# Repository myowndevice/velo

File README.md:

## Велокомпьютер

Велокомпьютер (англ. Cyclocomputer; в просторечии — Велосчётчик) — электронное устройство для измерения скорости и пробега велосипеда, а также дополнительных параметров, таких как средняя скорость, время в пути, максимальная скорость, каденс (частота вращения педалей) и другие.

Вы можете самостоятельно сделать этот современный прибор. Прибор базируется на микроконтроллере STM8 и позволит вам приобрести навыки программирования микроконтроллеров. Он имеет отличные, современные характеристики:

- Управление и передача информации по bluetooth (экран отсутствует), например на смартфон
- Учёт основных показателей — текущая скорость, максимальная скорость, активное время поездки, потраченные калории, пробег
- Питание от li-ion аккумулятора, зарядка по micro usb разъёму
- 2 датчика геркона— на колесо и педали
- Более 18 поездок по 3часа на одном заряде и более полугода в режиме хранения
- Автоматическое фиксирование поездки, спящий режим, автоматическое начало работы — нет необходимости включать, выключать.
- Расчёт и хранение основных показателей за 4 последние поездки— скорость, расход калорий, пробег, распределение скоростей по времени
- Звуковой контроль параметров — заданной скорости и каденса, нет необходимости все время смотреть за показателями.
- Компактный размер 30х50х35мм.

Данный репозитарий содержит все необходимые файлы для изготовления велокомпьютера.Если вы будете скачивать файлы через web не забудьте скачать общую папку Kicadlib.

Ознакомится со схемой и подробным описанием велокомпьютера, программы, и порядка сборки можно, [прочитав эту подробную статью](http://myowndevice.ru/index.php/pribory/item/1-velokompyuter)

Также [здесь](http://myowndevice.ru) вы найдете подробное описание как сделать другие приборы, много теории о том, как их делать, методику изготовления печатных плат и много другого.

Изучай микроконтроллеры, делай платы дома, разрабатывай электронику сам!

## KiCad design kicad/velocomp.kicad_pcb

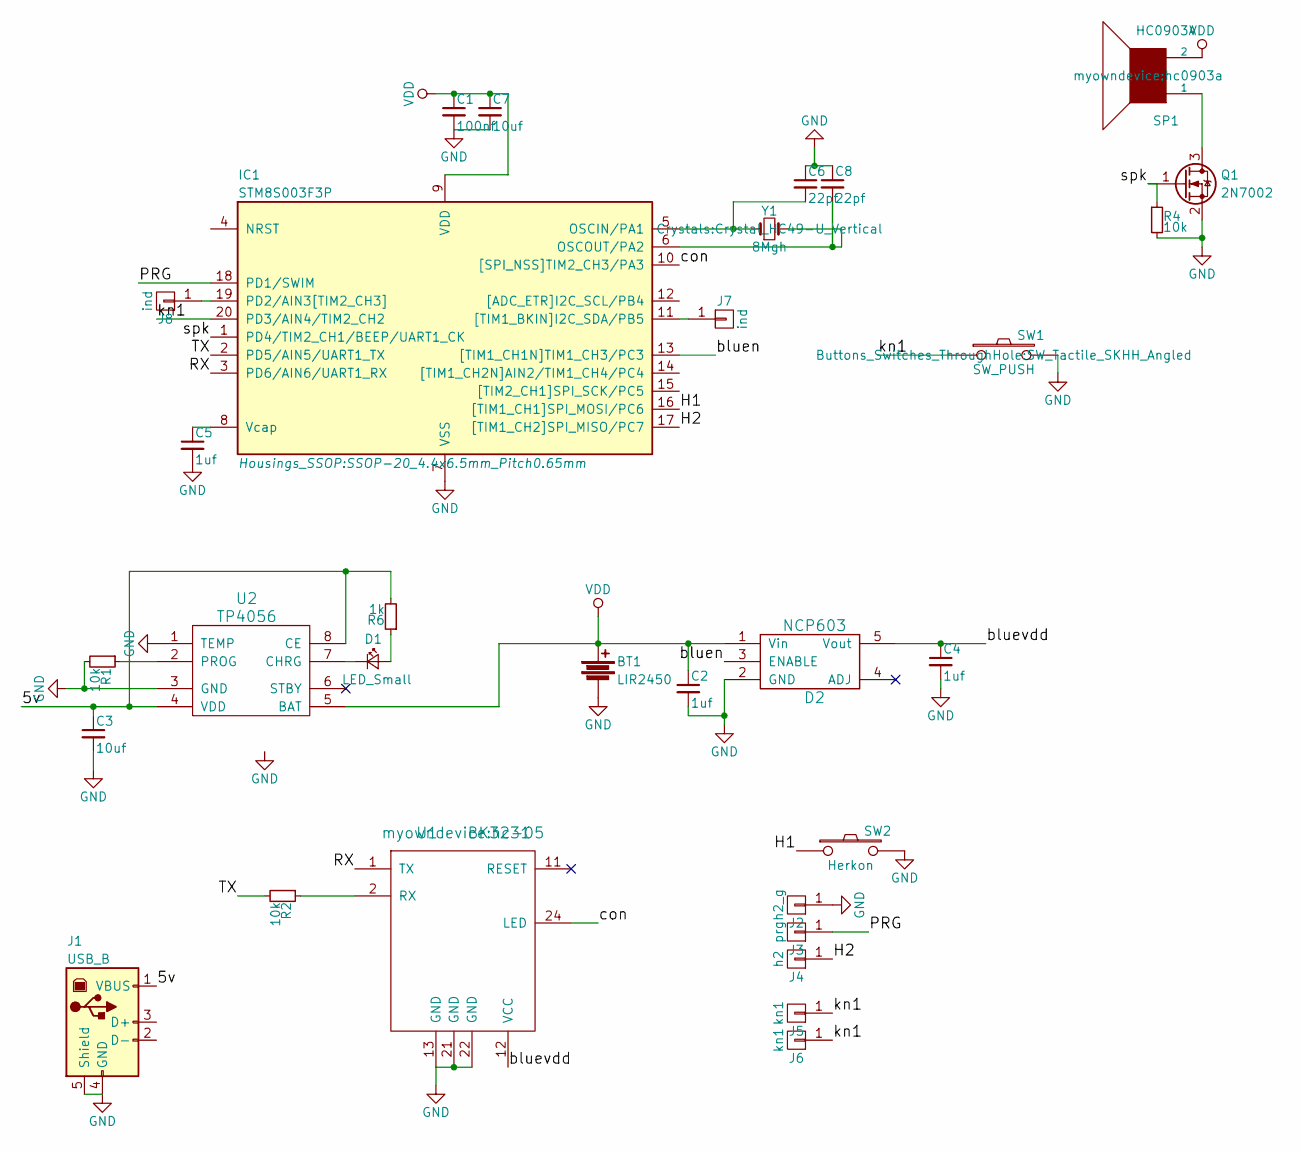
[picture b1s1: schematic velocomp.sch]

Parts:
BT1: LIR2450; Pin_Header_Straight_1x02
C1: 100nf; C_0603_HandSoldering
C2, C4, C5: 1uf; C_0805_HandSoldering
C3, C7: 10uf; C_0805_HandSoldering
C6, C8: 22pf; C_0603_HandSoldering
D1: LED_Small; LED_0603_HandSoldering
D2: NCP603; SOT-23-5
IC1: STM8S003F3P; SSOP-20_4.4x6.5mm_Pitch0.65mm
J1: USB_B; usb5s
J2: h2_g; wirepadme
J3: prg; wirepad_mini
J4: h2; wirepadme
J5, J6: kn1; wirepad_mini
J7, J8: ind; wirepad_mini
Q1: 2N7002; SOT-23
R1, R2, R4: 10k; R_0603_HandSoldering
R6: 1k; R_0603_HandSoldering
SP1: HC0903A; hc0903a
SW1: SW_PUSH; SW_Tactile_SKHH_Angled
SW2: Herkon; R_Bare_Metal_Element_L21.3mm_W4.8mm_P20.30mm
U1: BK3231; hc-05
U2: TP4056; SOIC-8-1EP_3.9x4.9mm_Pitch1.27mm
Y1: 8Mgh; Crystal_HC49-U_Vertical

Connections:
/5v: C3.1, J1.1 (VBUS), R6.2, U2.4 (VDD), U2.8 (CE)
/H1: IC1.16 ([TIM1_CH1]SPI_MOSI/PC6), SW2.1
/H2: IC1.17 ([TIM1_CH2]SPI_MISO/PC7), J4.1
/PRG: IC1.18 (PD1/SWIM), J3.1
/RX: IC1.3 (PD6/AIN6/UART1_RX), U1.1 (TX)
/TX: IC1.2 (PD5/AIN5/UART1_TX), R2.2
/bluen: D2.3 (ENABLE), IC1.13 ([TIM1_CH1N]TIM1_CH3/PC3)
/bluevdd: C4.1, D2.5 (Vout), U1.12 (VCC)
/con: IC1.10 ([SPI_NSS]TIM2_CH3/PA3), U1.24 (LED)
/kn1: IC1.20 (PD3/AIN4/TIM2_CH2), J5.1, J6.1, SW1.1
/spk: IC1.1 (PD4/TIM2_CH1/BEEP/UART1_CK), Q1.1 (G), R4.1
GND: BT1.2, C1.2, C2.2, C3.2, C4.2, C5.2, C6.1, C7.2, C8.1, D2.2 (GND), IC1.7 (VSS), J1.4 (GND), J1.5 (Shield), J2.1, Q1.2 (S), R1.2, R4.2, SW1.2, SW2.2, U1.13 (GND), U1.21 (GND), U1.22 (GND), U2.1 (TEMP), U2.3 (GND), U2.9 (GND)
unnamed: C5.1, IC1.8 (Vcap)
unnamed: C6.2, IC1.5 (OSCIN/PA1), Y1.1
unnamed: C8.2, IC1.6 (OSCOUT/PA2), Y1.2
unnamed: D1.1 (K), U2.7 (CHRG)
unnamed: D1.2 (A), R6.1
unnamed: IC1.11 ([TIM1_BKIN]I2C_SDA/PB5), J7.1
unnamed: IC1.19 (PD2/AIN3[TIM2_CH3]), J8.1
unnamed: Q1.3 (D), SP1.1
unnamed: R1.1, U2.2 (PROG)
unnamed: R2.1, U1.2 (RX)
VDD: BT1.1, C1.1, C2.1, C7.1, D2.1 (Vin), IC1.9 (VDD), SP1.2, U2.5 (BAT)

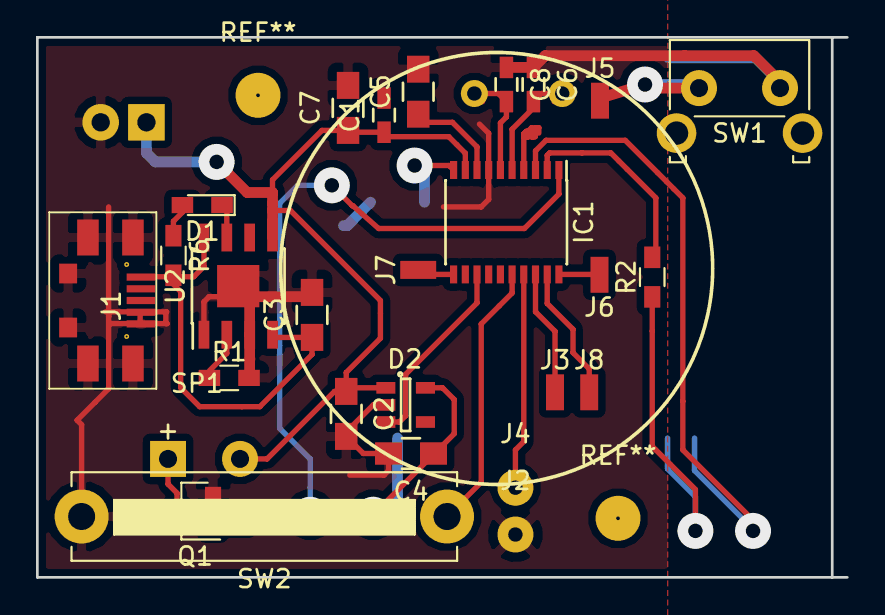
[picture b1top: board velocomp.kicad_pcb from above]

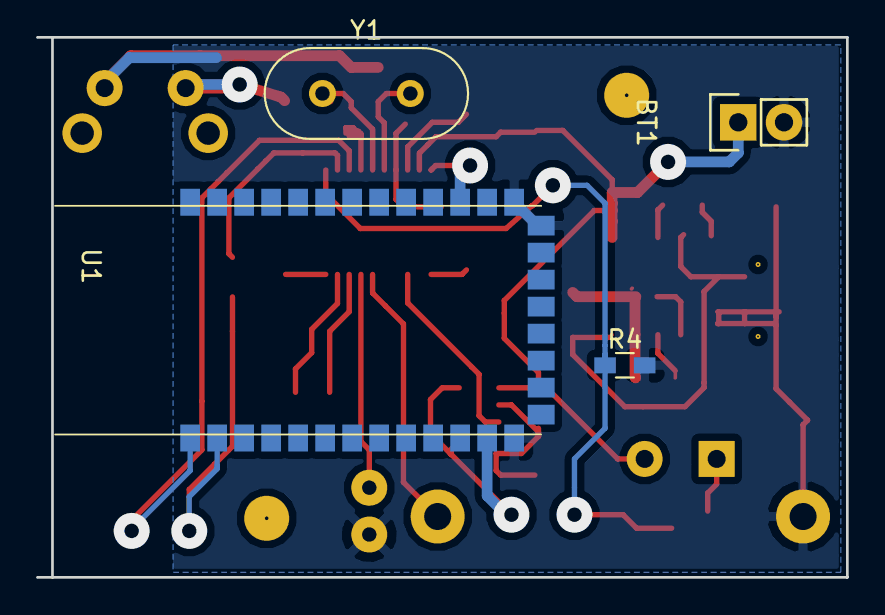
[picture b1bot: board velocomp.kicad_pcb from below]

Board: 2 copper layers, 45.0 x 30.0 mm, 31 parts (4 on the bottom side), 23 nets.

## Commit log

2017-10-15 start
